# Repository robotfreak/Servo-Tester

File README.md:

# Introduction

An ESP32-S3 based Servo Tester.

# Hardware

* Waveshare ESP32-S3 Zero
* 1.3" OLED Display SSH1106
* Rotary Encoder with button
* 5 x 3x1 pin header 

# Software

* Arduino IDE 2.x
* Espressif ESP32 board library
* Adafruit_GFX library
* Adafruit_SH110x library
* s3servo library https://github.com/Rob58329/ESP32S3servo.git
*  Encoder library https://github.com/PaulStoffregen/Encoder

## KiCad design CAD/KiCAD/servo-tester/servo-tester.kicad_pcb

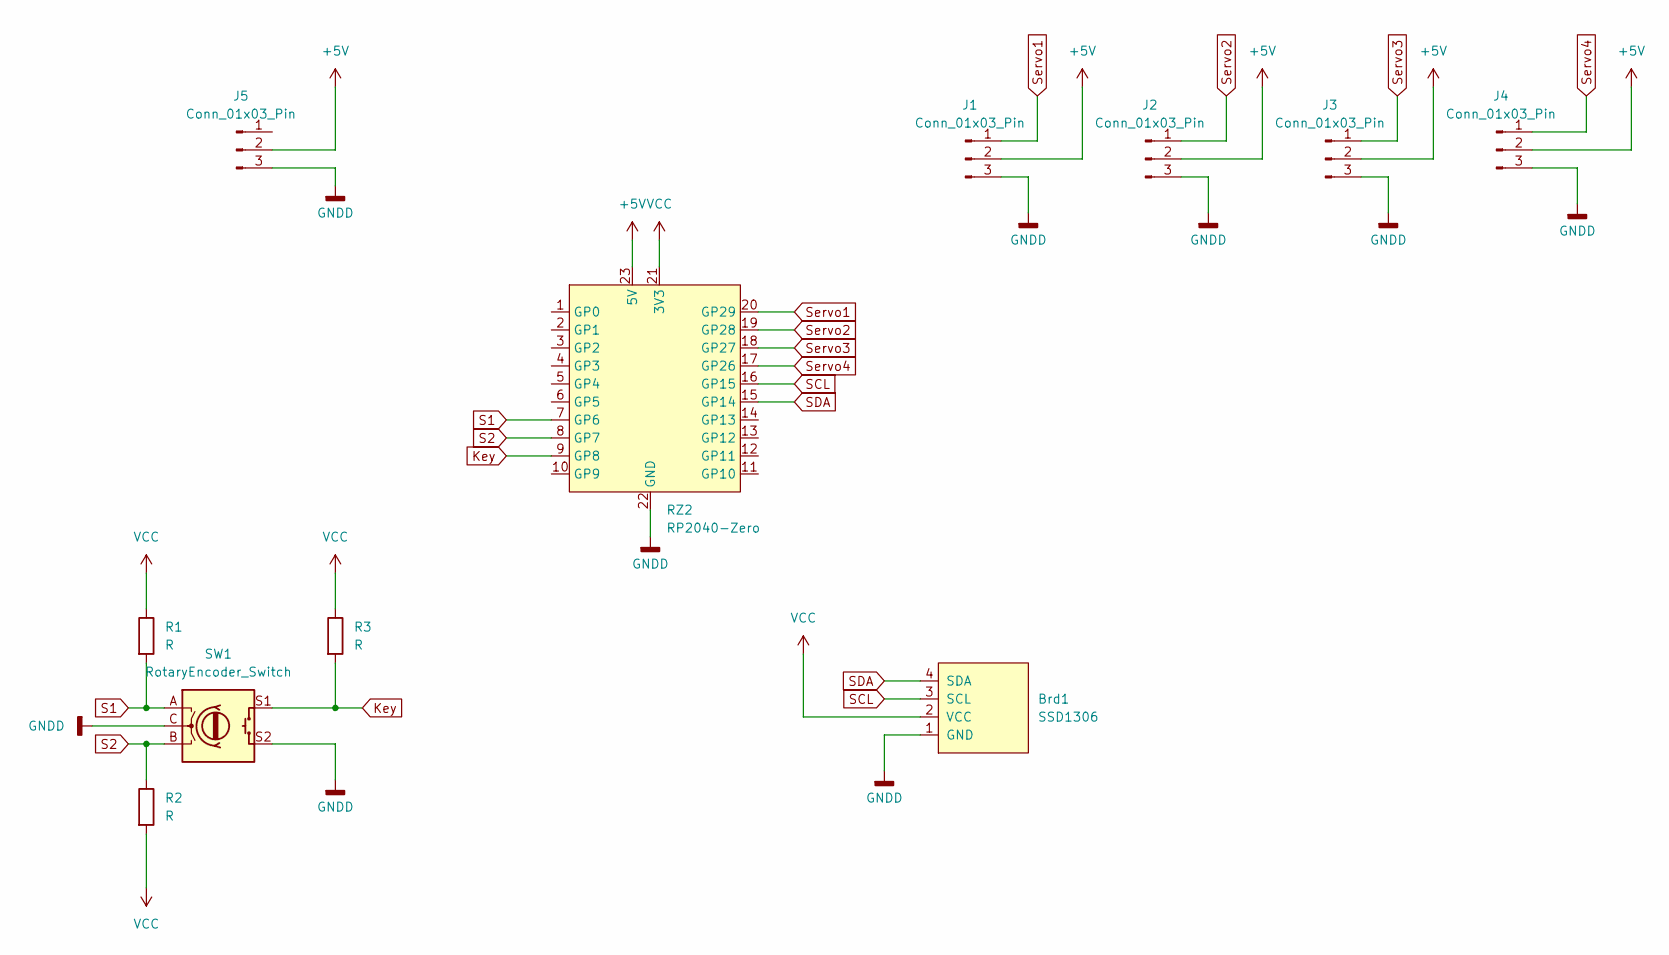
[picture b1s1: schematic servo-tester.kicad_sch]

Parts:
Brd1: SSD1306; 128x64OLED
J1, J2, J3, J4: Conn_01x03_Pin; PinHeader_1x03_P2.54mm_Vertical
J5: Conn_01x03_Pin; PinHeader_1x03_P2.54mm_Horizontal
R1, R2, R3: R; R_1206_3216Metric
RZ2: RP2040-Zero
SW1: RotaryEncoder_Switch; RotaryEncoder_Alps_EC11E-Switch_Vertical_H20mm_CircularMoun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

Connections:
+5V: J1.2, J2.2, J3.2, J4.2, J5.2, RZ2.23 (5V)
GNDD: Brd1.1 (GND), J1.3, J2.3, J3.3, J4.3, J5.3, RZ2.22 (GND), SW1.C, SW1.S2
Key: R3.2, RZ2.9 (GP8), SW1.S1
S1: R1.2, RZ2.7 (GP6), SW1.A
S2: R2.1, RZ2.8 (GP7), SW1.B
SCL: Brd1.3 (SCL), RZ2.16 (GP15)
SDA: Brd1.4 (SDA), RZ2.15 (GP14)
Servo1: J1.1, RZ2.20 (GP29)
Servo2: J2.1, RZ2.19 (GP28)
Servo3: J3.1, RZ2.18 (GP27)
Servo4: J4.1, RZ2.17 (GP26)
VCC: Brd1.2 (VCC), R1.1, R2.2, R3.1, RZ2.21 (3V3)

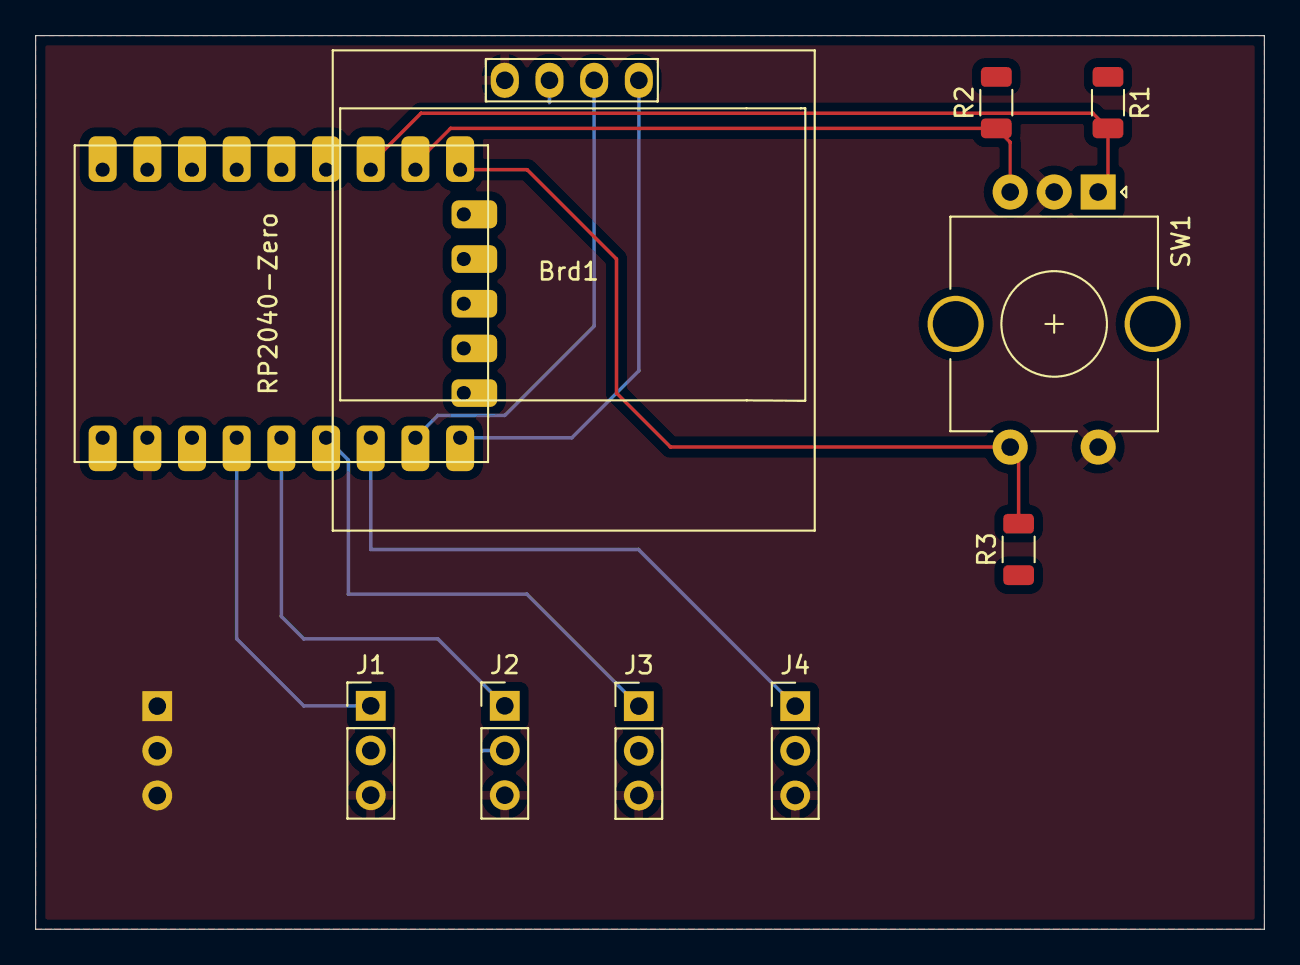
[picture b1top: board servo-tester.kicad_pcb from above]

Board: 2 copper layers, 69.8 x 50.8 mm, 11 parts (1 on the bottom side), 12 nets.

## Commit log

2024-09-21 add display mode in microseconds
2024-09-21 updated readme docu
2024-09-22 added pos and sweep butoon
2024-09-23 Aktualisieren von README.md
2024-09-23 added images
